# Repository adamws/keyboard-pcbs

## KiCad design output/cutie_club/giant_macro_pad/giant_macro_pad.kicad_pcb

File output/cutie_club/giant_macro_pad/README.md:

## cutie_club/giant_macro_pad

[layout](giant_macro_pad-kle.json) - [PCB](giant_macro_pad.kicad_pcb)

{:loading="lazy"}

[Open in keyboard-layout-editor](http://www.keyboard-layout-editor.com/##@@=0,%200&=0,%201&=0,%202&=0,%203&=0,%204&=0,%205&=0,%206&=0,%207&=0,%208&=0,%209&=0,%2010&=0,%2011&=0,%2012&=0,%2013&=0,%2014&=0,%2015&=0,%2016&=0,%2017&=0,%2018&=0,%2019;&@=1,%200&=1,%201&=1,%202&=1,%203&=1,%204&=1,%205&=1,%206&=1,%207&=1,%208&=1,%209&=1,%2010&=1,%2011&=1,%2012&=1,%2013&=1,%2014&=1,%2015&=1,%2016&=1,%2017&=1,%2018&=1,%2019;&@=2,%200&=2,%201&=2,%202&=2,%203&=2,%204&=2,%205&=2,%206&=2,%207&=2,%208&=2,%209&=2,%2010&=2,%2011&=2,%2012&=2,%2013&=2,%2014&=2,%2015&=2,%2016&=2,%2017&=2,%2018&=2,%2019;&@=3,%200&=3,%201&=3,%202&=3,%203&=3,%204&=3,%205&=3,%206&=3,%207&=3,%208&=3,%209&=3,%2010&=3,%2011&=3,%2012&=3,%2013&=3,%2014&=3,%2015&=3,%2016&=3,%2017&=3,%2018&=3,%2019;&@=4,%200&=4,%201&=4,%202&=4,%203&=4,%204&=4,%205&=4,%206&=4,%207&=4,%208&=4,%209&=4,%2010&=4,%2011&=4,%2012&=4,%2013&=4,%2014&=4,%2015&=4,%2016&=4,%2017&=4,%2018&=4,%2019;&@=5,%200&=5,%201&=5,%202&=5,%203&=5,%204&=5,%205&=5,%206&=5,%207&=5,%208&=5,%209&=5,%2010&=5,%2011&=5,%2012&=5,%2013&=5,%2014&=5,%2015&=5,%2016&=5,%2017&=5,%2018&=5,%2019;&@=6,%200&=6,%201&=6,%202&=6,%203&=6,%204&=6,%205&=6,%206&=6,%207&=6,%208&=6,%209&=6,%2010&=6,%2011&=6,%2012&=6,%2013&=6,%2014&=6,%2015&=6,%2016&=6,%2017&=6,%2018&=6,%2019;&@=7,%200&=7,%201&=7,%202&=7,%203&=7,%204&=7,%205&=7,%206&=7,%207&=7,%208&=7,%209&=7,%2010&=7,%2011&=7,%2012&=7,%2013&=7,%2014&=7,%2015&=7,%2016&=7,%2017&=7,%2018&=7,%2019;&@=8,%200&=8,%201&=8,%202&=8,%203&=8,%204&=8,%205&=8,%206&=8,%207&=8,%208&=8,%209&=8,%2010&=8,%2011&=8,%2012&=8,%2013&=8,%2014&=8,%2015&=8,%2016&=8,%2017&=8,%2018&=8,%2019;&@=9,%200&=9,%201&=9,%202&=9,%203&=9,%204&=9,%205&=9,%206&=9,%207&=9,%208&=9,%209&=9,%2010&=9,%2011&=9,%2012&=9,%2013&=9,%2014&=9,%2015&=9,%2016&=9,%2017&=9,%2018&=9,%2019;&@=10,%200&=10,%201&=10,%202&=10,%203&=10,%204&=10,%205&=10,%206&=10,%207&=10,%208&=10,%209&=10,%2010&=10,%2011&=10,%2012&=10,%2013&=10,%2014&=10,%2015&=10,%2016&=10,%2017&=10,%2018&=10,%2019;&@=11,%200&=11,%201&=11,%202&=11,%203&=11,%204&=11,%205&=11,%206&=11,%207&=11,%208&=11,%209&=11,%2010&=11,%2011&=11,%2012&=11,%2013&=11,%2014&=11,%2015&=11,%2016&=11,%2017&=11,%2018&=11,%2019;&@=12,%200&=12,%201&=12,%202&=12,%203&=12,%204&=12,%205&=12,%206&=12,%207&=12,%208&=12,%209&=12,%2010&=12,%2011&=12,%2012&=12,%2013&=12,%2014&=12,%2015&=12,%2016&=12,%2017&=12,%2018&=12,%2019;&@=13,%200&=13,%201&=13,%202&=13,%203&=13,%204&=13,%205&=13,%206&=13,%207&=13,%208&=13,%209&=13,%2010&=13,%2011&=13,%2012&=13,%2013&=13,%2014&=13,%2015&=13,%2016&=13,%2017&=13,%2018&=13,%2019;&@=14,%200&=14,%201&=14,%202&=14,%203&=14,%204&=14,%205&=14,%206&=14,%207&=14,%208&=14,%209&=14,%2010&=14,%2011&=14,%2012&=14,%2013&=14,%2014&=14,%2015&=14,%2016&=14,%2017&=14,%2018&=14,%2019;&@=15,%200&=15,%201&=15,%202&=15,%203&=15,%204&=15,%205&=15,%206&=15,%207&=15,%208&=15,%209&=15,%2010&=15,%2011&=15,%2012&=15,%2013&=15,%2014&=15,%2015&=15,%2016&=15,%2017&=15,%2018&=15,%2019;&@=16,%200&=16,%201&=16,%202&=16,%203&=16,%204&=16,%205&=16,%206&=16,%207&=16,%208&=16,%209&=16,%2010&=16,%2011&=16,%2012&=16,%2013&=16,%2014&=16,%2015&=16,%2016&=16,%2017&=16,%2018&=16,%2019;&@=17,%200&=17,%201&=17,%202&=17,%203&=17,%204&=17,%205&=17,%206&=17,%207&=17,%208&=17,%209&=17,%2010&=17,%2011&=17,%2012&=17,%2013&=17,%2014&=17,%2015&=17,%2016&=17,%2017&=17,%2018&=17,%2019;&@=18,%200&=18,%201&=18,%202&=18,%203&=18,%204&=18,%205&=18,%206&=18,%207&=18,%208&=18,%209&=18,%2010&=18,%2011&=18,%2012&=18,%2013&=18,%2014&=18,%2015&=18,%2016&=18,%2017&=18,%2018&=18,%2019;&@=19,%200&=19,%201&=19,%202&=19,%203&=19,%204&=19,%205&=19,%206&=19,%207&=19,%208&=19,%209&=19,%2010&=19,%2011&=19,%2012&=19,%2013&=19,%2014&=19,%2015&=19,%2016&=19,%2017&=19,%2018&=19,%2019)

{:loading="lazy"}

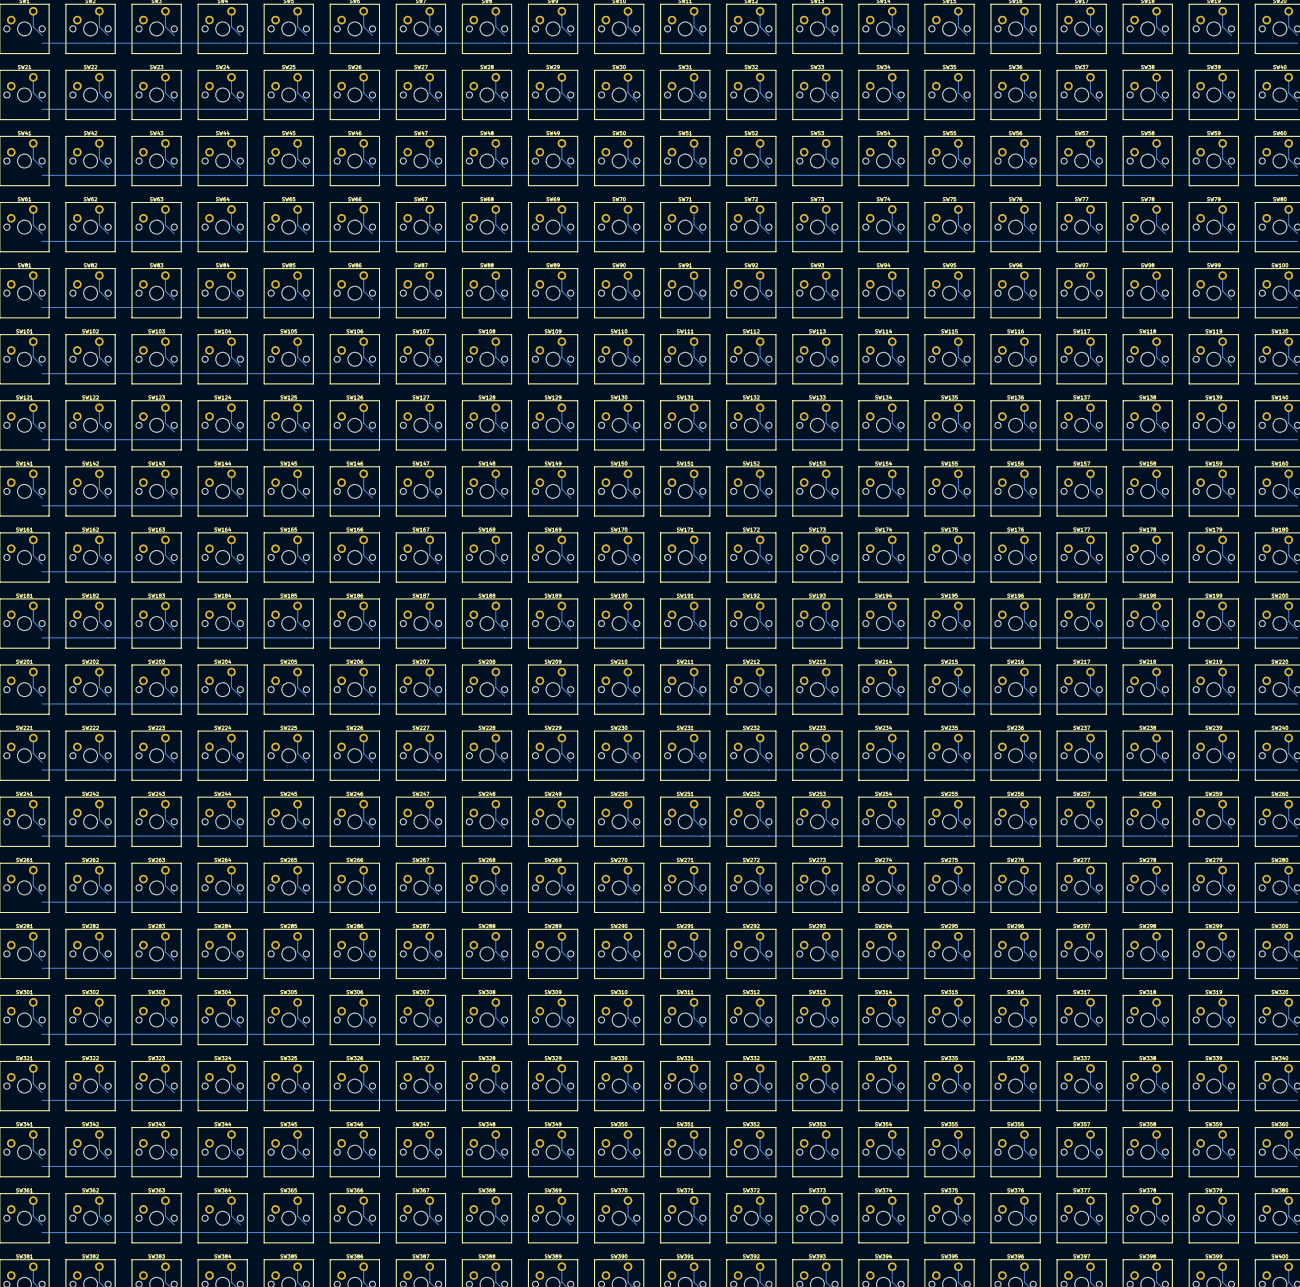
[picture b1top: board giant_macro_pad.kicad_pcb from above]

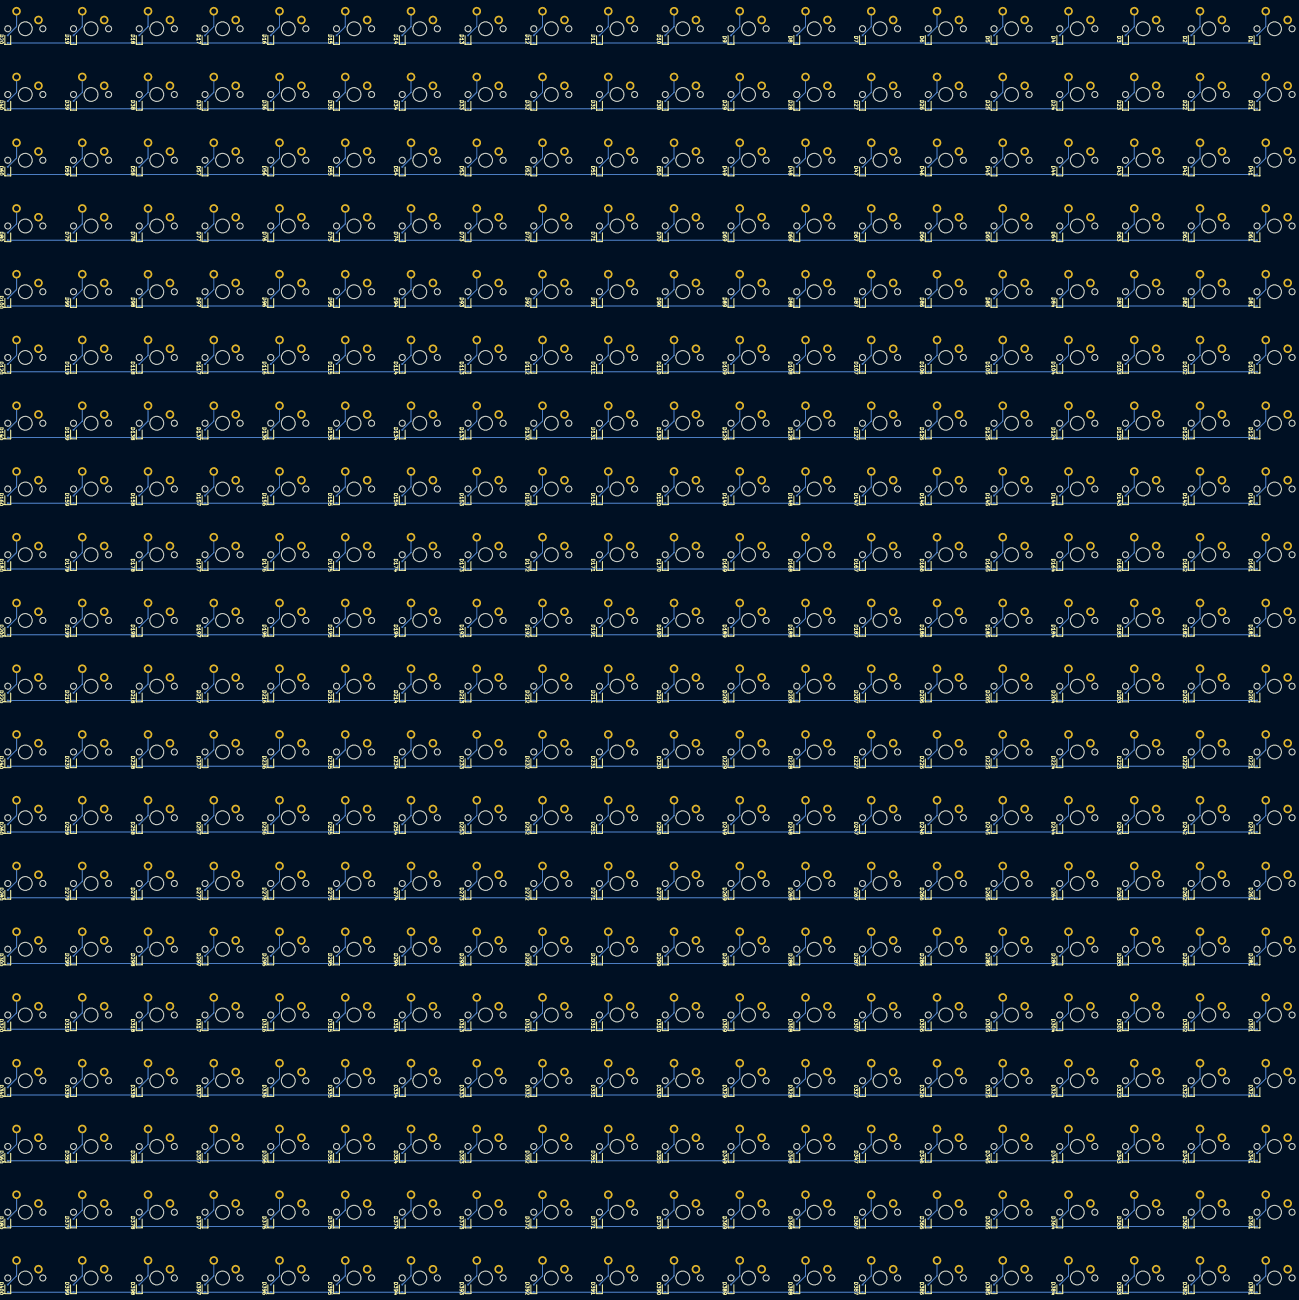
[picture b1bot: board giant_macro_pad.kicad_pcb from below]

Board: 2 copper layers, 800 parts (400 on the bottom side), 440 nets.

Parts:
D1, D2, D3, D4, D5, D6, D7, D8, D9, D10, D11, D12, D13, D14, D15, D16, D17, D18, D19, D20, D21, D22, D23, D24, D25, D26, D27, D28, D29, D30, D31, D32, D33, D34, D35, D36, D37, D38, D39, D40, D41, D42, D43, D44, D45, D46, D47, D48, D49, D50, D51, D52, D53, D54, D55, D56, D57, D58, D59, D60, D61, D62, D63, D64, D65, D66, D67, D68, D69, D70, D71, D72, D73, D74, D75, D76, D77, D78, D79, D80, D81, D82, D83, D84, D85, D86, D87, D88, D89, D90, D91, D92, D93, D94, D95, D96, D97, D98, D99, D100, D101, D102, D103, D104, D105, D106, D107, D108, D109, D110, D111, D112, D113, D114, D115, D116, D117, D118, D119, D120, D121, D122, D123, D124, D125, D126, D127, D128, D129, D130, D131, D132, D133, D134, D135, D136, D137, D138, D139, D140, D141, D142, D143, D144, D145, D146, D147, D148, D149, D150, D151, D152, D153, D154, D155, D156, D157, D158, D159, D160, D161, D162, D163, D164, D165, D166, D167, D168, D169, D170, D171, D172, D173, D174, D175, D176, D177, D178, D179, D180, D181, D182, D183, D184, D185, D186, D187, D188, D189, D190, D191, D192, D193, D194, D195, D196, D197, D198, D199, D200, D201, D202, D203, D204, D205, D206, D207, D208, D209, D210, D211, D212, D213, D214, D215, D216, D217, D218, D219, D220, D221, D222, D223, D224, D225, D226, D227, D228, D229, D230, D231, D232, D233, D234, D235, D236, D237, D238, D239, D240, D241, D242, D243, D244, D245, D246, D247, D248, D249, D250, D251, D252, D253, D254, D255, D256, D257, D258, D259, D260, D261, D262, D263, D264, D265, D266, D267, D268, D269, D270, D271, D272, D273, D274, D275, D276, D277, D278, D279, D280, D281, D282, D283, D284, D285, D286, D287, D288, D289, D290, D291, D292, D293, D294, D295, D296, D297, D298, D299, D300, D301, D302, D303, D304, D305, D306, D307, D308, D309, D310, D311, D312, D313, D314, D315, D316, D317, D318, D319, D320, D321, D322, D323, D324, D325, D326, D327, D328, D329, D330, D331, D332, D333, D334, D335, D336, D337, D338, D339, D340, D341, D342, D343, D344, D345, D346, D347, D348, D349, D350, D351, D352, D353, D354, D355, D356, D357, D358, D359, D360, D361, D362, D363, D364, D365, D366, D367, D368, D369, D370, D371, D372, D373, D374, D375, D376, D377, D378, D379, D380, D381, D382, D383, D384, D385, D386, D387, D388, D389, D390, D391, D392, D393, D394, D395, D396, D397, D398, D399, D400: D_SOD-323F
SW1, SW2, SW3, SW4, SW5, SW6, SW7, SW8, SW9, SW10, SW11, SW12, SW13, SW14, SW15, SW16, SW17, SW18, SW19, SW20, SW21, SW22, SW23, SW24, SW25, SW26, SW27, SW28, SW29, SW30, SW31, SW32, SW33, SW34, SW35, SW36, SW37, SW38, SW39, SW40, SW41, SW42, SW43, SW44, SW45, SW46, SW47, SW48, SW49, SW50, SW51, SW52, SW53, SW54, SW55, SW56, SW57, SW58, SW59, SW60, SW61, SW62, SW63, SW64, SW65, SW66, SW67, SW68, SW69, SW70, SW71, SW72, SW73, SW74, SW75, SW76, SW77, SW78, SW79, SW80, SW81, SW82, SW83, SW84, SW85, SW86, SW87, SW88, SW89, SW90, SW91, SW92, SW93, SW94, SW95, SW96, SW97, SW98, SW99, SW100, SW101, SW102, SW103, SW104, SW105, SW106, SW107, SW108, SW109, SW110, SW111, SW112, SW113, SW114, SW115, SW116, SW117, SW118, SW119, SW120, SW121, SW122, SW123, SW124, SW125, SW126, SW127, SW128, SW129, SW130, SW131, SW132, SW133, SW134, SW135, SW136, SW137, SW138, SW139, SW140, SW141, SW142, SW143, SW144, SW145, SW146, SW147, SW148, SW149, SW150, SW151, SW152, SW153, SW154, SW155, SW156, SW157, SW158, SW159, SW160, SW161, SW162, SW163, SW164, SW165, SW166, SW167, SW168, SW169, SW170, SW171, SW172, SW173, SW174, SW175, SW176, SW177, SW178, SW179, SW180, SW181, SW182, SW183, SW184, SW185, SW186, SW187, SW188, SW189, SW190, SW191, SW192, SW193, SW194, SW195, SW196, SW197, SW198, SW199, SW200, SW201, SW202, SW203, SW204, SW205, SW206, SW207, SW208, SW209, SW210, SW211, SW212, SW213, SW214, SW215, SW216, SW217, SW218, SW219, SW220, SW221, SW222, SW223, SW224, SW225, SW226, SW227, SW228, SW229, SW230, SW231, SW232, SW233, SW234, SW235, SW236, SW237, SW238, SW239, SW240, SW241, SW242, SW243, SW244, SW245, SW246, SW247, SW248, SW249, SW250, SW251, SW252, SW253, SW254, SW255, SW256, SW257, SW258, SW259, SW260, SW261, SW262, SW263, SW264, SW265, SW266, SW267, SW268, SW269, SW270, SW271, SW272, SW273, SW274, SW275, SW276, SW277, SW278, SW279, SW280, SW281, SW282, SW283, SW284, SW285, SW286, SW287, SW288, SW289, SW290, SW291, SW292, SW293, SW294, SW295, SW296, SW297, SW298, SW299, SW300, SW301, SW302, SW303, SW304, SW305, SW306, SW307, SW308, SW309, SW310, SW311, SW312, SW313, SW314, SW315, SW316, SW317, SW318, SW319, SW320, SW321, SW322, SW323, SW324, SW325, SW326, SW327, SW328, SW329, SW330, SW331, SW332, SW333, SW334, SW335, SW336, SW337, SW338, SW339, SW340, SW341, SW342, SW343, SW344, SW345, SW346, SW347, SW348, SW349, SW350, SW351, SW352, SW353, SW354, SW355, SW356, SW357, SW358, SW359, SW360, SW361, SW362, SW363, SW364, SW365, SW366, SW367, SW368, SW369, SW370, SW371, SW372, SW373, SW374, SW375, SW376, SW377, SW378, SW379, SW380, SW381, SW382, SW383, SW384, SW385, SW386, SW387, SW388, SW389, SW390, SW391, SW392, SW393, SW394, SW395, SW396, SW397, SW398, SW399, SW400: SW_Cherry_MX_PCB_1.00u

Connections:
COL 0: SW1.1, SW21.1, SW41.1, SW61.1, SW81.1, SW101.1, SW121.1, SW141.1, SW161.1, SW181.1, SW201.1, SW221.1, SW241.1, SW261.1, SW281.1, SW301.1, SW321.1, SW341.1, SW361.1, SW381.1
COL 1: SW2.1, SW22.1, SW42.1, SW62.1, SW82.1, SW102.1, SW122.1, SW142.1, SW162.1, SW182.1, SW202.1, SW222.1, SW242.1, SW262.1, SW282.1, SW302.1, SW322.1, SW342.1, SW362.1, SW382.1
COL 2: SW3.1, SW23.1, SW43.1, SW63.1, SW83.1, SW103.1, SW123.1, SW143.1, SW163.1, SW183.1, SW203.1, SW223.1, SW243.1, SW263.1, SW283.1, SW303.1, SW323.1, SW343.1, SW363.1, SW383.1
COL 3: SW4.1, SW24.1, SW44.1, SW64.1, SW84.1, SW104.1, SW124.1, SW144.1, SW164.1, SW184.1, SW204.1, SW224.1, SW244.1, SW264.1, SW284.1, SW304.1, SW324.1, SW344.1, SW364.1, SW384.1
COL 4: SW5.1, SW25.1, SW45.1, SW65.1, SW85.1, SW105.1, SW125.1, SW145.1, SW165.1, SW185.1, SW205.1, SW225.1, SW245.1, SW265.1, SW285.1, SW305.1, SW325.1, SW345.1, SW365.1, SW385.1
COL 5: SW6.1, SW26.1, SW46.1, SW66.1, SW86.1, SW106.1, SW126.1, SW146.1, SW166.1, SW186.1, SW206.1, SW226.1, SW246.1, SW266.1, SW286.1, SW306.1, SW326.1, SW346.1, SW366.1, SW386.1
COL 6: SW7.1, SW27.1, SW47.1, SW67.1, SW87.1, SW107.1, SW127.1, SW147.1, SW167.1, SW187.1, SW207.1, SW227.1, SW247.1, SW267.1, SW287.1, SW307.1, SW327.1, SW347.1, SW367.1, SW387.1
COL 7: SW8.1, SW28.1, SW48.1, SW68.1, SW88.1, SW108.1, SW128.1, SW148.1, SW168.1, SW188.1, SW208.1, SW228.1, SW248.1, SW268.1, SW288.1, SW308.1, SW328.1, SW348.1, SW368.1, SW388.1
COL 8: SW9.1, SW29.1, SW49.1, SW69.1, SW89.1, SW109.1, SW129.1, SW149.1, SW169.1, SW189.1, SW209.1, SW229.1, SW249.1, SW269.1, SW289.1, SW309.1, SW329.1, SW349.1, SW369.1, SW389.1
COL 9: SW10.1, SW30.1, SW50.1, SW70.1, SW90.1, SW110.1, SW130.1, SW150.1, SW170.1, SW190.1, SW210.1, SW230.1, SW250.1, SW270.1, SW290.1, SW310.1, SW330.1, SW350.1, SW370.1, SW390.1
COL 10: SW11.1, SW31.1, SW51.1, SW71.1, SW91.1, SW111.1, SW131.1, SW151.1, SW171.1, SW191.1, SW211.1, SW231.1, SW251.1, SW271.1, SW291.1, SW311.1, SW331.1, SW351.1, SW371.1, SW391.1
COL 11: SW12.1, SW32.1, SW52.1, SW72.1, SW92.1, SW112.1, SW132.1, SW152.1, SW172.1, SW192.1, SW212.1, SW232.1, SW252.1, SW272.1, SW292.1, SW312.1, SW332.1, SW352.1, SW372.1, SW392.1
COL 12: SW13.1, SW33.1, SW53.1, SW73.1, SW93.1, SW113.1, SW133.1, SW153.1, SW173.1, SW193.1, SW213.1, SW233.1, SW253.1, SW273.1, SW293.1, SW313.1, SW333.1, SW353.1, SW373.1, SW393.1
COL 13: SW14.1, SW34.1, SW54.1, SW74.1, SW94.1, SW114.1, SW134.1, SW154.1, SW174.1, SW194.1, SW214.1, SW234.1, SW254.1, SW274.1, SW294.1, SW314.1, SW334.1, SW354.1, SW374.1, SW394.1
COL 14: SW15.1, SW35.1, SW55.1, SW75.1, SW95.1, SW115.1, SW135.1, SW155.1, SW175.1, SW195.1, SW215.1, SW235.1, SW255.1, SW275.1, SW295.1, SW315.1, SW335.1, SW355.1, SW375.1, SW395.1
COL 15: SW16.1, SW36.1, SW56.1, SW76.1, SW96.1, SW116.1, SW136.1, SW156.1, SW176.1, SW196.1, SW216.1, SW236.1, SW256.1, SW276.1, SW296.1, SW316.1, SW336.1, SW356.1, SW376.1, SW396.1
COL 16: SW17.1, SW37.1, SW57.1, SW77.1, SW97.1, SW117.1, SW137.1, SW157.1, SW177.1, SW197.1, SW217.1, SW237.1, SW257.1, SW277.1, SW297.1, SW317.1, SW337.1, SW357.1, SW377.1, SW397.1
COL 17: SW18.1, SW38.1, SW58.1, SW78.1, SW98.1, SW118.1, SW138.1, SW158.1, SW178.1, SW198.1, SW218.1, SW238.1, SW258.1, SW278.1, SW298.1, SW318.1, SW338.1, SW358.1, SW378.1, SW398.1
COL 18: SW19.1, SW39.1, SW59.1, SW79.1, SW99.1, SW119.1, SW139.1, SW159.1, SW179.1, SW199.1, SW219.1, SW239.1, SW259.1, SW279.1, SW299.1, SW319.1, SW339.1, SW359.1, SW379.1, SW399.1
COL 19: SW20.1, SW40.1, SW60.1, SW80.1, SW100.1, SW120.1, SW140.1, SW160.1, SW180.1, SW200.1, SW220.1, SW240.1, SW260.1, SW280.1, SW300.1, SW320.1, SW340.1, SW360.1, SW380.1, SW400.1
unnamed: D1.2, SW1.2
unnamed: D2.2, SW2.2
unnamed: D3.2, SW3.2
unnamed: D4.2, SW4.2
unnamed: D5.2, SW5.2
unnamed: D6.2, SW6.2
unnamed: D7.2, SW7.2
unnamed: D8.2, SW8.2
unnamed: D9.2, SW9.2
unnamed: D10.2, SW10.2
unnamed: D11.2, SW11.2
unnamed: D12.2, SW12.2
unnamed: D13.2, SW13.2
unnamed: D14.2, SW14.2
unnamed: D15.2, SW15.2
unnamed: D16.2, SW16.2
unnamed: D17.2, SW17.2
unnamed: D18.2, SW18.2
unnamed: D19.2, SW19.2
unnamed: D20.2, SW20.2
unnamed: D21.2, SW21.2
unnamed: D22.2, SW22.2
unnamed: D23.2, SW23.2
unnamed: D24.2, SW24.2
unnamed: D25.2, SW25.2
unnamed: D26.2, SW26.2
unnamed: D27.2, SW27.2
unnamed: D28.2, SW28.2
unnamed: D29.2, SW29.2
unnamed: D30.2, SW30.2
unnamed: D31.2, SW31.2
unnamed: D32.2, SW32.2
unnamed: D33.2, SW33.2
unnamed: D34.2, SW34.2
unnamed: D35.2, SW35.2
unnamed: D36.2, SW36.2
unnamed: D37.2, SW37.2
unnamed: D38.2, SW38.2
unnamed: D39.2, SW39.2
unnamed: D40.2, SW40.2
unnamed: D41.2, SW41.2
unnamed: D42.2, SW42.2
unnamed: D43.2, SW43.2
unnamed: D44.2, SW44.2
unnamed: D45.2, SW45.2
unnamed: D46.2, SW46.2
unnamed: D47.2, SW47.2
unnamed: D48.2, SW48.2
unnamed: D49.2, SW49.2
unnamed: D50.2, SW50.2
unnamed: D51.2, SW51.2
unnamed: D52.2, SW52.2
unnamed: D53.2, SW53.2
unnamed: D54.2, SW54.2
unnamed: D55.2, SW55.2
unnamed: D56.2, SW56.2
unnamed: D57.2, SW57.2
unnamed: D58.2, SW58.2
unnamed: D59.2, SW59.2
unnamed: D60.2, SW60.2
unnamed: D61.2, SW61.2
unnamed: D62.2, SW62.2
unnamed: D63.2, SW63.2
unnamed: D64.2, SW64.2
unnamed: D65.2, SW65.2
unnamed: D66.2, SW66.2
unnamed: D67.2, SW67.2
unnamed: D68.2, SW68.2
unnamed: D69.2, SW69.2
unnamed: D70.2, SW70.2
unnamed: D71.2, SW71.2
unnamed: D72.2, SW72.2
unnamed: D73.2, SW73.2
unnamed: D74.2, SW74.2
unnamed: D75.2, SW75.2
unnamed: D76.2, SW76.2
unnamed: D77.2, SW77.2
unnamed: D78.2, SW78.2
unnamed: D79.2, SW79.2
unnamed: D80.2, SW80.2
unnamed: D81.2, SW81.2
unnamed: D82.2, SW82.2
unnamed: D83.2, SW83.2
unnamed: D84.2, SW84.2
unnamed: D85.2, SW85.2
unnamed: D86.2, SW86.2
unnamed: D87.2, SW87.2
unnamed: D88.2, SW88.2
unnamed: D89.2, SW89.2
unnamed: D90.2, SW90.2
unnamed: D91.2, SW91.2
unnamed: D92.2, SW92.2
unnamed: D93.2, SW93.2
unnamed: D94.2, SW94.2
unnamed: D95.2, SW95.2
unnamed: D96.2, SW96.2
unnamed: D97.2, SW97.2
unnamed: D98.2, SW98.2
unnamed: D99.2, SW99.2
unnamed: D100.2, SW100.2
unnamed: D101.2, SW101.2
unnamed: D102.2, SW102.2
unnamed: D103.2, SW103.2
unnamed: D104.2, SW104.2
unnamed: D105.2, SW105.2
unnamed: D106.2, SW106.2
unnamed: D107.2, SW107.2
unnamed: D108.2, SW108.2
unnamed: D109.2, SW109.2
unnamed: D110.2, SW110.2
unnamed: D111.2, SW111.2
unnamed: D112.2, SW112.2
unnamed: D113.2, SW113.2
unnamed: D114.2, SW114.2
unnamed: D115.2, SW115.2
unnamed: D116.2, SW116.2
unnamed: D117.2, SW117.2
unnamed: D118.2, SW118.2
unnamed: D119.2, SW119.2
unnamed: D120.2, SW120.2
unnamed: D121.2, SW121.2
unnamed: D122.2, SW122.2
unnamed: D123.2, SW123.2
unnamed: D124.2, SW124.2
unnamed: D125.2, SW125.2
unnamed: D126.2, SW126.2
unnamed: D127.2, SW127.2
unnamed: D128.2, SW128.2
unnamed: D129.2, SW129.2
unnamed: D130.2, SW130.2
unnamed: D131.2, SW131.2
unnamed: D132.2, SW132.2
unnamed: D133.2, SW133.2
unnamed: D134.2, SW134.2
unnamed: D135.2, SW135.2
unnamed: D136.2, SW136.2
unnamed: D137.2, SW137.2
unnamed: D138.2, SW138.2
unnamed: D139.2, SW139.2
unnamed: D140.2, SW140.2
unnamed: D141.2, SW141.2
unnamed: D142.2, SW142.2
unnamed: D143.2, SW143.2
unnamed: D144.2, SW144.2
unnamed: D145.2, SW145.2
unnamed: D146.2, SW146.2
unnamed: D147.2, SW147.2
unnamed: D148.2, SW148.2
unnamed: D149.2, SW149.2
unnamed: D150.2, SW150.2
unnamed: D151.2, SW151.2
unnamed: D152.2, SW152.2
unnamed: D153.2, SW153.2
unnamed: D154.2, SW154.2
unnamed: D155.2, SW155.2
unnamed: D156.2, SW156.2
unnamed: D157.2, SW157.2
unnamed: D158.2, SW158.2
unnamed: D159.2, SW159.2
unnamed: D160.2, SW160.2
unnamed: D161.2, SW161.2
unnamed: D162.2, SW162.2
unnamed: D163.2, SW163.2
unnamed: D164.2, SW164.2
unnamed: D165.2, SW165.2
unnamed: D166.2, SW166.2
unnamed: D167.2, SW167.2
unnamed: D168.2, SW168.2
unnamed: D169.2, SW169.2
unnamed: D170.2, SW170.2
unnamed: D171.2, SW171.2
unnamed: D172.2, SW172.2
unnamed: D173.2, SW173.2
unnamed: D174.2, SW174.2
unnamed: D175.2, SW175.2
unnamed: D176.2, SW176.2
unnamed: D177.2, SW177.2
unnamed: D178.2, SW178.2
unnamed: D179.2, SW179.2
unnamed: D180.2, SW180.2
unnamed: D181.2, SW181.2
unnamed: D182.2, SW182.2
unnamed: D183.2, SW183.2
unnamed: D184.2, SW184.2
unnamed: D185.2, SW185.2
unnamed: D186.2, SW186.2
unnamed: D187.2, SW187.2
unnamed: D188.2, SW188.2
unnamed: D189.2, SW189.2
unnamed: D190.2, SW190.2
unnamed: D191.2, SW191.2
unnamed: D192.2, SW192.2
unnamed: D193.2, SW193.2
unnamed: D194.2, SW194.2
unnamed: D195.2, SW195.2
unnamed: D196.2, SW196.2
unnamed: D197.2, SW197.2
unnamed: D198.2, SW198.2
unnamed: D199.2, SW199.2
unnamed: D200.2, SW200.2
unnamed: D201.2, SW201.2
unnamed: D202.2, SW202.2
unnamed: D203.2, SW203.2
unnamed: D204.2, SW204.2
unnamed: D205.2, SW205.2
unnamed: D206.2, SW206.2
unnamed: D207.2, SW207.2
unnamed: D208.2, SW208.2
unnamed: D209.2, SW209.2
unnamed: D210.2, SW210.2
unnamed: D211.2, SW211.2
unnamed: D212.2, SW212.2
unnamed: D213.2, SW213.2
unnamed: D214.2, SW214.2
unnamed: D215.2, SW215.2
unnamed: D216.2, SW216.2
unnamed: D217.2, SW217.2
unnamed: D218.2, SW218.2
unnamed: D219.2, SW219.2
unnamed: D220.2, SW220.2
unnamed: D221.2, SW221.2
unnamed: D222.2, SW222.2
unnamed: D223.2, SW223.2
unnamed: D224.2, SW224.2
unnamed: D225.2, SW225.2
unnamed: D226.2, SW226.2
unnamed: D227.2, SW227.2
unnamed: D228.2, SW228.2
unnamed: D229.2, SW229.2
unnamed: D230.2, SW230.2
unnamed: D231.2, SW231.2
unnamed: D232.2, SW232.2
unnamed: D233.2, SW233.2
unnamed: D234.2, SW234.2
unnamed: D235.2, SW235.2
unnamed: D236.2, SW236.2
unnamed: D237.2, SW237.2
unnamed: D238.2, SW238.2
unnamed: D239.2, SW239.2
unnamed: D240.2, SW240.2
unnamed: D241.2, SW241.2
unnamed: D242.2, SW242.2
unnamed: D243.2, SW243.2
unnamed: D244.2, SW244.2
unnamed: D245.2, SW245.2
unnamed: D246.2, SW246.2
unnamed: D247.2, SW247.2
unnamed: D248.2, SW248.2
unnamed: D249.2, SW249.2
unnamed: D250.2, SW250.2
unnamed: D251.2, SW251.2
unnamed: D252.2, SW252.2
unnamed: D253.2, SW253.2
unnamed: D254.2, SW254.2
unnamed: D255.2, SW255.2
unnamed: D256.2, SW256.2
unnamed: D257.2, SW257.2
unnamed: D258.2, SW258.2
unnamed: D259.2, SW259.2
unnamed: D260.2, SW260.2
unnamed: D261.2, SW261.2
unnamed: D262.2, SW262.2
unnamed: D263.2, SW263.2
unnamed: D264.2, SW264.2
unnamed: D265.2, SW265.2
unnamed: D266.2, SW266.2
unnamed: D267.2, SW267.2
unnamed: D268.2, SW268.2
unnamed: D269.2, SW269.2
unnamed: D270.2, SW270.2
unnamed: D271.2, SW271.2
unnamed: D272.2, SW272.2
unnamed: D273.2, SW273.2
unnamed: D274.2, SW274.2
unnamed: D275.2, SW275.2
unnamed: D276.2, SW276.2
unnamed: D277.2, SW277.2
unnamed: D278.2, SW278.2
unnamed: D279.2, SW279.2
unnamed: D280.2, SW280.2
unnamed: D281.2, SW281.2
unnamed: D282.2, SW282.2
unnamed: D283.2, SW283.2
unnamed: D284.2, SW284.2
unnamed: D285.2, SW285.2
unnamed: D286.2, SW286.2
unnamed: D287.2, SW287.2
unnamed: D288.2, SW288.2
unnamed: D289.2, SW289.2
unnamed: D290.2, SW290.2
unnamed: D291.2, SW291.2
unnamed: D292.2, SW292.2
unnamed: D293.2, SW293.2
unnamed: D294.2, SW294.2
unnamed: D295.2, SW295.2
unnamed: D296.2, SW296.2
unnamed: D297.2, SW297.2
unnamed: D298.2, SW298.2
unnamed: D299.2, SW299.2
unnamed: D300.2, SW300.2
unnamed: D301.2, SW301.2
unnamed: D302.2, SW302.2
unnamed: D303.2, SW303.2
unnamed: D304.2, SW304.2
unnamed: D305.2, SW305.2
unnamed: D306.2, SW306.2
unnamed: D307.2, SW307.2
unnamed: D308.2, SW308.2
unnamed: D309.2, SW309.2
unnamed: D310.2, SW310.2
unnamed: D311.2, SW311.2
unnamed: D312.2, SW312.2
unnamed: D313.2, SW313.2
unnamed: D314.2, SW314.2
unnamed: D315.2, SW315.2
unnamed: D316.2, SW316.2
unnamed: D317.2, SW317.2
unnamed: D318.2, SW318.2
unnamed: D319.2, SW319.2
unnamed: D320.2, SW320.2
unnamed: D321.2, SW321.2
unnamed: D322.2, SW322.2
unnamed: D323.2, SW323.2
unnamed: D324.2, SW324.2
unnamed: D325.2, SW325.2
unnamed: D326.2, SW326.2
unnamed: D327.2, SW327.2
unnamed: D328.2, SW328.2
unnamed: D329.2, SW329.2
unnamed: D330.2, SW330.2
unnamed: D331.2, SW331.2
unnamed: D332.2, SW332.2
unnamed: D333.2, SW333.2
unnamed: D334.2, SW334.2
unnamed: D335.2, SW335.2
unnamed: D336.2, SW336.2
unnamed: D337.2, SW337.2
unnamed: D338.2, SW338.2
unnamed: D339.2, SW339.2
unnamed: D340.2, SW340.2
unnamed: D341.2, SW341.2
unnamed: D342.2, SW342.2
unnamed: D343.2, SW343.2
unnamed: D344.2, SW344.2
unnamed: D345.2, SW345.2
unnamed: D346.2, SW346.2
unnamed: D347.2, SW347.2
unnamed: D348.2, SW348.2
unnamed: D349.2, SW349.2
unnamed: D350.2, SW350.2
unnamed: D351.2, SW351.2
unnamed: D352.2, SW352.2
unnamed: D353.2, SW353.2
unnamed: D354.2, SW354.2
unnamed: D355.2, SW355.2
unnamed: D356.2, SW356.2
unnamed: D357.2, SW357.2
unnamed: D358.2, SW358.2
unnamed: D359.2, SW359.2
unnamed: D360.2, SW360.2
unnamed: D361.2, SW361.2
unnamed: D362.2, SW362.2
unnamed: D363.2, SW363.2
unnamed: D364.2, SW364.2
unnamed: D365.2, SW365.2
unnamed: D366.2, SW366.2
unnamed: D367.2, SW367.2
unnamed: D368.2, SW368.2
unnamed: D369.2, SW369.2
unnamed: D370.2, SW370.2
unnamed: D371.2, SW371.2
unnamed: D372.2, SW372.2
unnamed: D373.2, SW373.2
unnamed: D374.2, SW374.2
unnamed: D375.2, SW375.2
unnamed: D376.2, SW376.2
unnamed: D377.2, SW377.2
unnamed: D378.2, SW378.2
unnamed: D379.2, SW379.2
unnamed: D380.2, SW380.2
unnamed: D381.2, SW381.2
unnamed: D382.2, SW382.2
unnamed: D383.2, SW383.2
unnamed: D384.2, SW384.2
unnamed: D385.2, SW385.2
unnamed: D386.2, SW386.2
unnamed: D387.2, SW387.2
unnamed: D388.2, SW388.2
unnamed: D389.2, SW389.2
unnamed: D390.2, SW390.2
unnamed: D391.2, SW391.2
unnamed: D392.2, SW392.2
unnamed: D393.2, SW393.2
unnamed: D394.2, SW394.2
unnamed: D395.2, SW395.2
unnamed: D396.2, SW396.2
unnamed: D397.2, SW397.2
unnamed: D398.2, SW398.2
unnamed: D399.2, SW399.2
unnamed: D400.2, SW400.2
ROW0: D1.1, D2.1, D3.1, D4.1, D5.1, D6.1, D7.1, D8.1, D9.1, D10.1, D11.1, D12.1, D13.1, D14.1, D15.1, D16.1, D17.1, D18.1, D19.1, D20.1
ROW1: D21.1, D22.1, D23.1, D24.1, D25.1, D26.1, D27.1, D28.1, D29.1, D30.1, D31.1, D32.1, D33.1, D34.1, D35.1, D36.1, D37.1, D38.1, D39.1, D40.1
ROW2: D41.1, D42.1, D43.1, D44.1, D45.1, D46.1, D47.1, D48.1, D49.1, D50.1, D51.1, D52.1, D53.1, D54.1, D55.1, D56.1, D57.1, D58.1, D59.1, D60.1
ROW3: D61.1, D62.1, D63.1, D64.1, D65.1, D66.1, D67.1, D68.1, D69.1, D70.1, D71.1, D72.1, D73.1, D74.1, D75.1, D76.1, D77.1, D78.1, D79.1, D80.1
ROW4: D81.1, D82.1, D83.1, D84.1, D85.1, D86.1, D87.1, D88.1, D89.1, D90.1, D91.1, D92.1, D93.1, D94.1, D95.1, D96.1, D97.1, D98.1, D99.1, D100.1
ROW5: D101.1, D102.1, D103.1, D104.1, D105.1, D106.1, D107.1, D108.1, D109.1, D110.1, D111.1, D112.1, D113.1, D114.1, D115.1, D116.1, D117.1, D118.1, D119.1, D120.1
ROW6: D121.1, D122.1, D123.1, D124.1, D125.1, D126.1, D127.1, D128.1, D129.1, D130.1, D131.1, D132.1, D133.1, D134.1, D135.1, D136.1, D137.1, D138.1, D139.1, D140.1
ROW7: D141.1, D142.1, D143.1, D144.1, D145.1, D146.1, D147.1, D148.1, D149.1, D150.1, D151.1, D152.1, D153.1, D154.1, D155.1, D156.1, D157.1, D158.1, D159.1, D160.1
ROW8: D161.1, D162.1, D163.1, D164.1, D165.1, D166.1, D167.1, D168.1, D169.1, D170.1, D171.1, D172.1, D173.1, D174.1, D175.1, D176.1, D177.1, D178.1, D179.1, D180.1
ROW9: D181.1, D182.1, D183.1, D184.1, D185.1, D186.1, D187.1, D188.1, D189.1, D190.1, D191.1, D192.1, D193.1, D194.1, D195.1, D196.1, D197.1, D198.1, D199.1, D200.1
ROW10: D201.1, D202.1, D203.1, D204.1, D205.1, D206.1, D207.1, D208.1, D209.1, D210.1, D211.1, D212.1, D213.1, D214.1, D215.1, D216.1, D217.1, D218.1, D219.1, D220.1
ROW11: D221.1, D222.1, D223.1, D224.1, D225.1, D226.1, D227.1, D228.1, D229.1, D230.1, D231.1, D232.1, D233.1, D234.1, D235.1, D236.1, D237.1, D238.1, D239.1, D240.1
ROW12: D241.1, D242.1, D243.1, D244.1, D245.1, D246.1, D247.1, D248.1, D249.1, D250.1, D251.1, D252.1, D253.1, D254.1, D255.1, D256.1, D257.1, D258.1, D259.1, D260.1
ROW13: D261.1, D262.1, D263.1, D264.1, D265.1, D266.1, D267.1, D268.1, D269.1, D270.1, D271.1, D272.1, D273.1, D274.1, D275.1, D276.1, D277.1, D278.1, D279.1, D280.1
ROW14: D281.1, D282.1, D283.1, D284.1, D285.1, D286.1, D287.1, D288.1, D289.1, D290.1, D291.1, D292.1, D293.1, D294.1, D295.1, D296.1, D297.1, D298.1, D299.1, D300.1
ROW15: D301.1, D302.1, D303.1, D304.1, D305.1, D306.1, D307.1, D308.1, D309.1, D310.1, D311.1, D312.1, D313.1, D314.1, D315.1, D316.1, D317.1, D318.1, D319.1, D320.1
ROW16: D321.1, D322.1, D323.1, D324.1, D325.1, D326.1, D327.1, D328.1, D329.1, D330.1, D331.1, D332.1, D333.1, D334.1, D335.1, D336.1, D337.1, D338.1, D339.1, D340.1
ROW17: D341.1, D342.1, D343.1, D344.1, D345.1, D346.1, D347.1, D348.1, D349.1, D350.1, D351.1, D352.1, D353.1, D354.1, D355.1, D356.1, D357.1, D358.1, D359.1, D360.1
ROW18: D361.1, D362.1, D363.1, D364.1, D365.1, D366.1, D367.1, D368.1, D369.1, D370.1, D371.1, D372.1, D373.1, D374.1, D375.1, D376.1, D377.1, D378.1, D379.1, D380.1
ROW19: D381.1, D382.1, D383.1, D384.1, D385.1, D386.1, D387.1, D388.1, D389.1, D390.1, D391.1, D392.1, D393.1, D394.1, D395.1, D396.1, D397.1, D398.1, D399.1, D400.1
